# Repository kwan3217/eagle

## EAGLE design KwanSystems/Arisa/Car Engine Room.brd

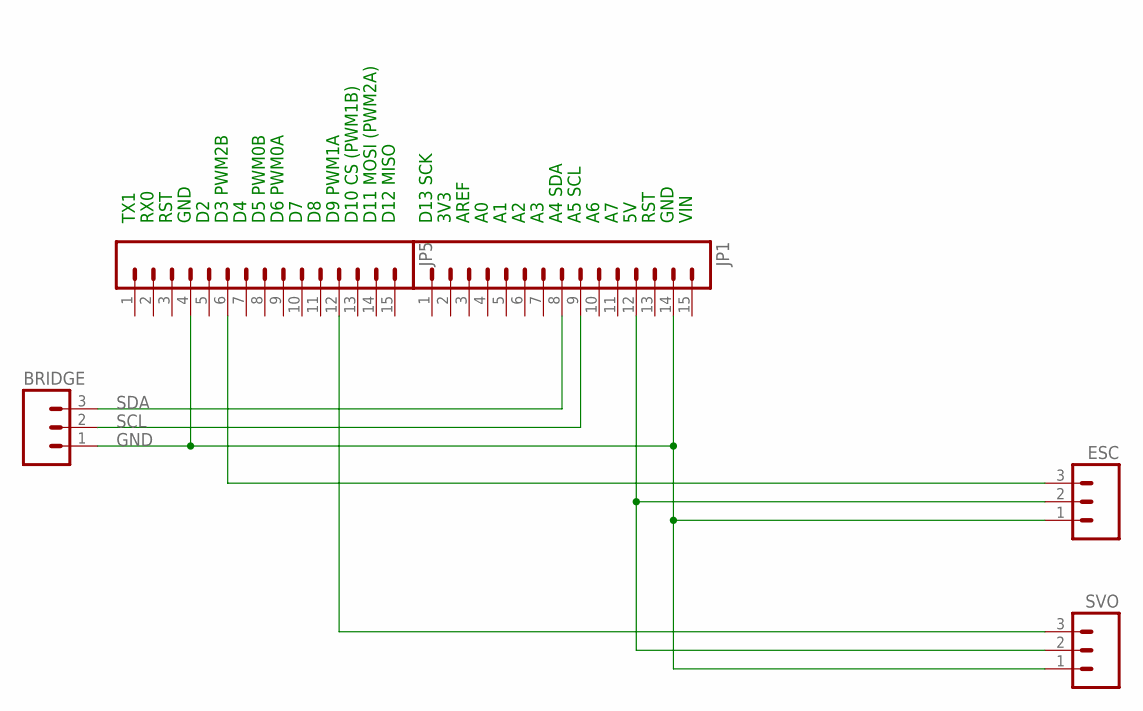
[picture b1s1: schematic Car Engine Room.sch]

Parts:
BRIDGE: M03PTH; 1X03
ESC: M03PTH; 1X03
JP1, JP5: M15; 1X15
SVO: M03PTH; 1X03

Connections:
GND: BRIDGE.1, ESC.1, JP1.14, JP5.4, SVO.1
IN1: ESC.3, JP5.6
IN2: JP5.12, SVO.3
SCL: BRIDGE.2, JP1.9
SDA: BRIDGE.3, JP1.8
VCC: ESC.2, JP1.12, SVO.2

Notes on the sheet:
VIN
GND
RST
A5 SCL
A4 SDA
AREF
3V3
D13 SCK
D12 MISO
D11 MOSI (PWM2A)
D10 CS (PWM1B)
D9 PWM1A
D6 PWM0A
D5 PWM0B
D3 PWM2B
RX0
TX1

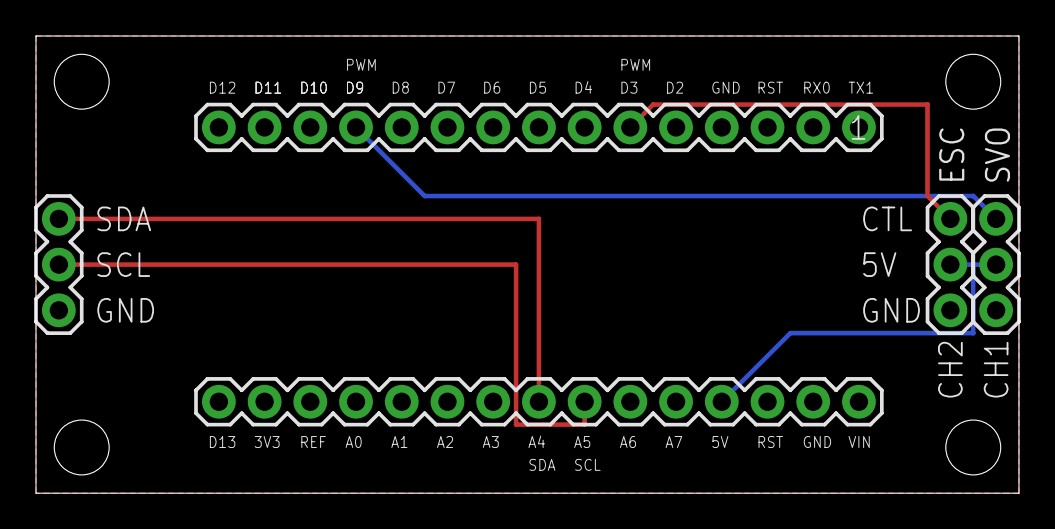
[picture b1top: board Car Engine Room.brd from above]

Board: 2 copper layers, 54.6 x 25.4 mm, 10 parts (1 on the bottom side), 6 nets.

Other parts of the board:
U$1, U$2, U$4, U$5: STAND-OFF-TIGHT
U$3: KWAN_CIRCLE

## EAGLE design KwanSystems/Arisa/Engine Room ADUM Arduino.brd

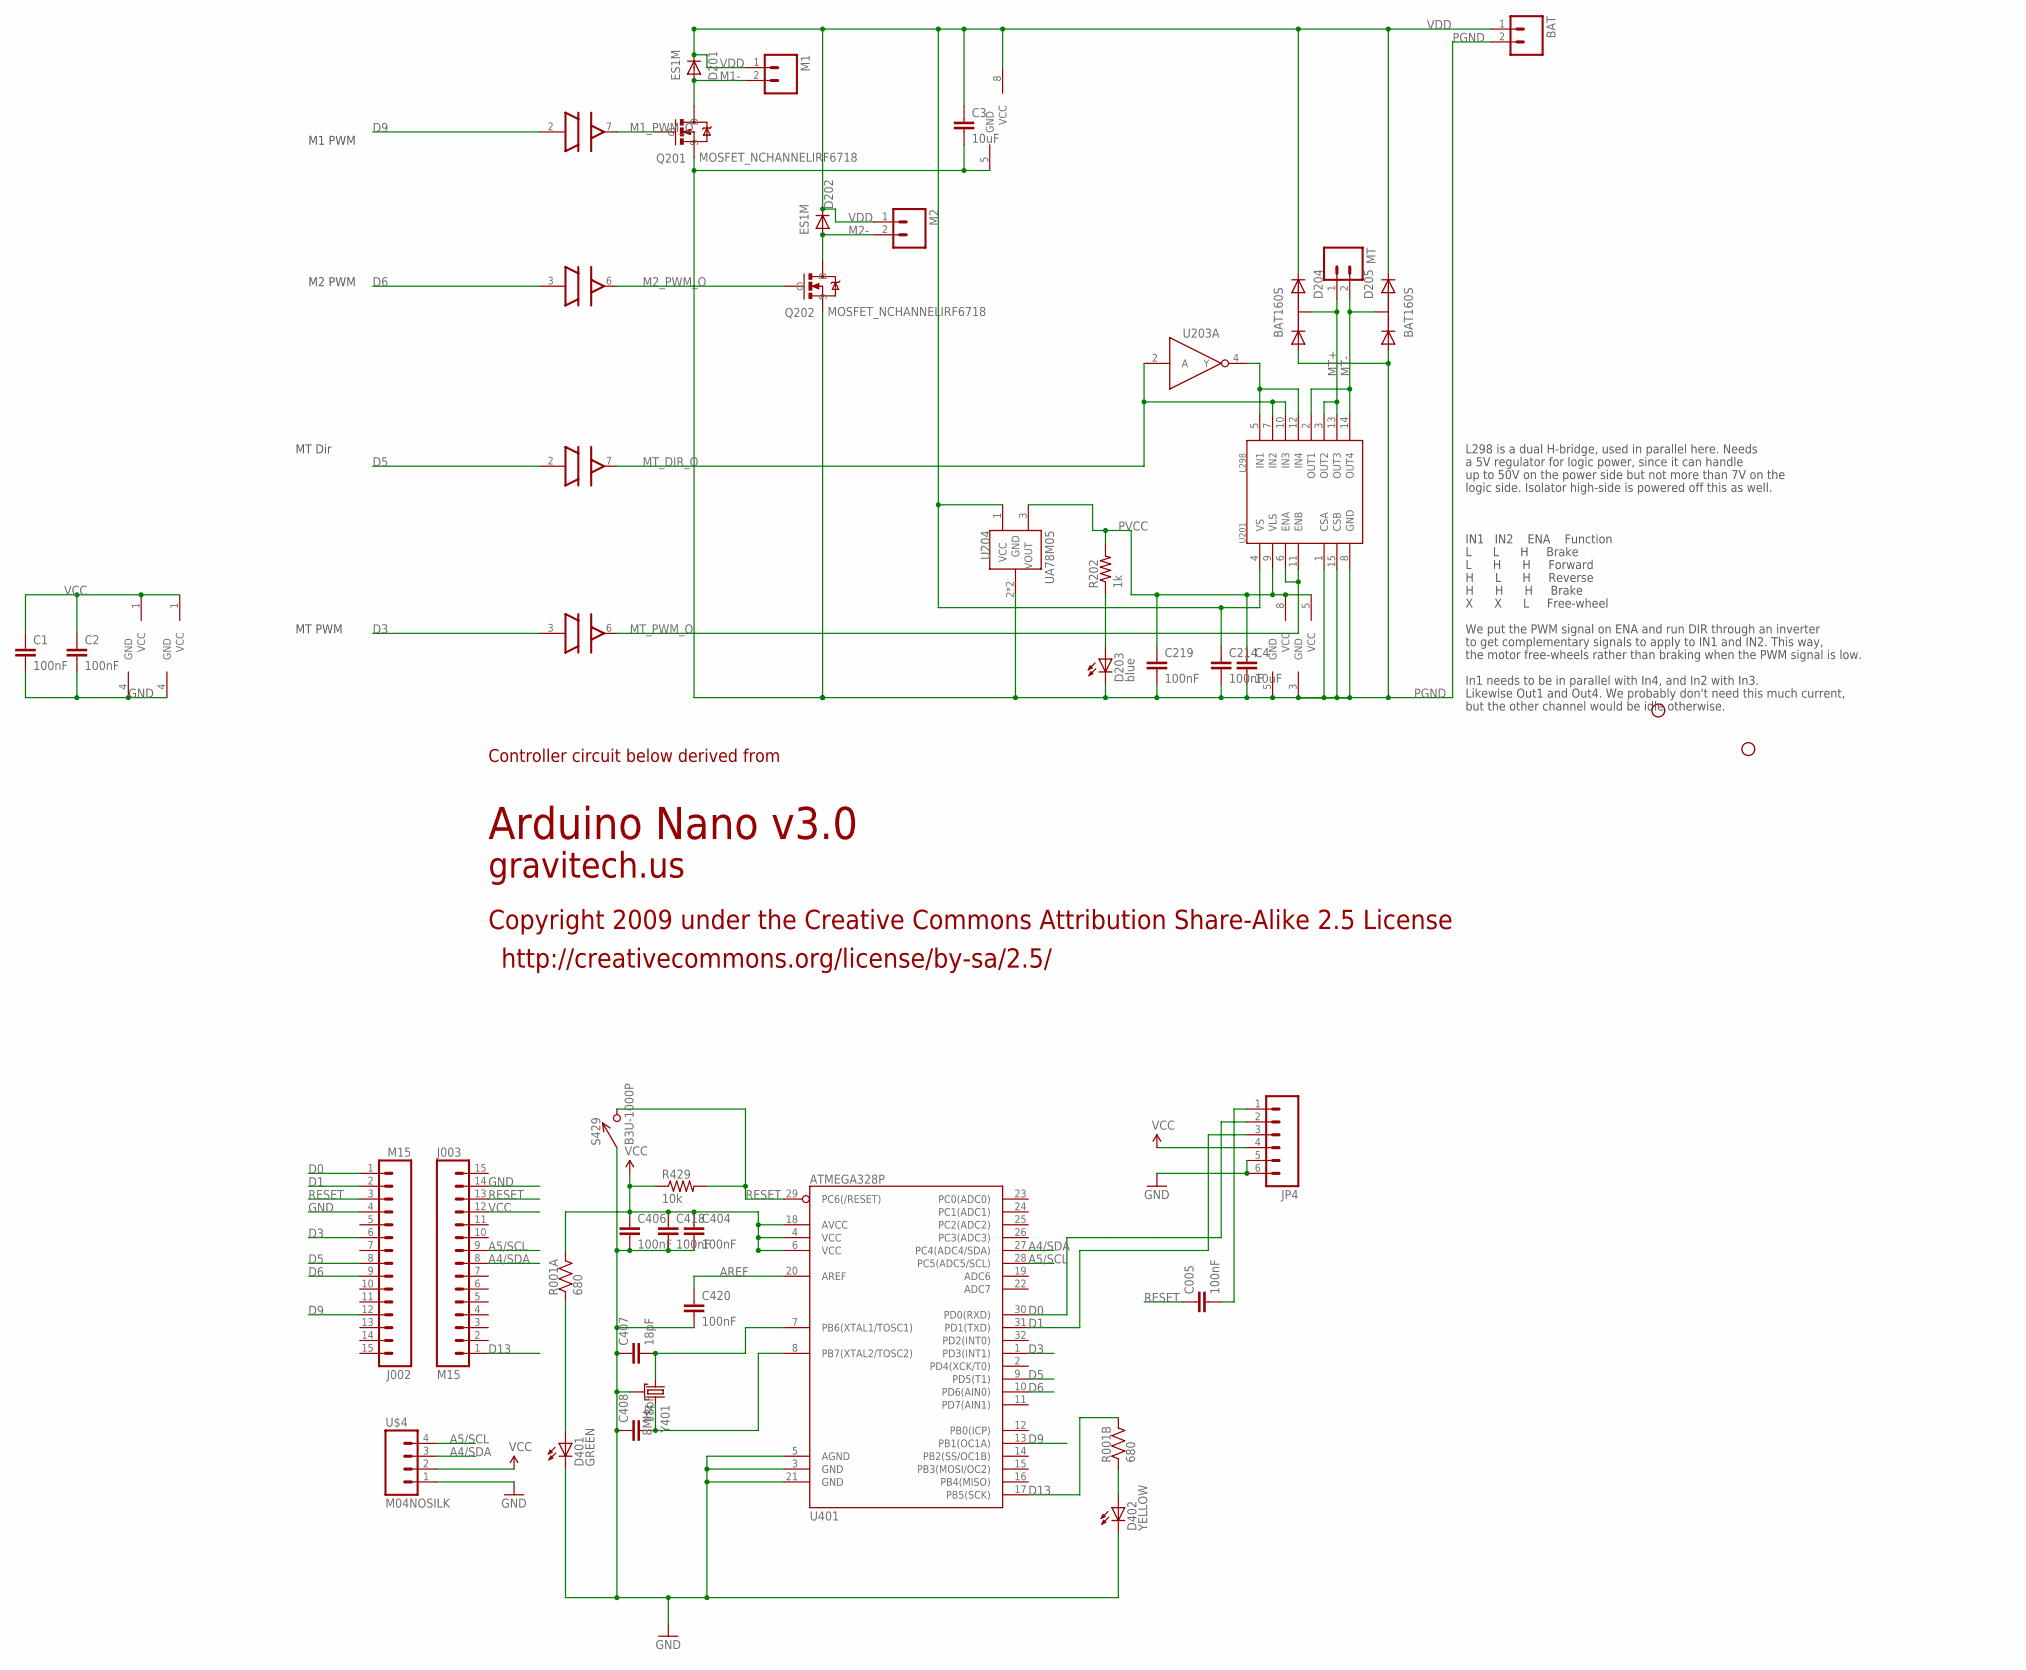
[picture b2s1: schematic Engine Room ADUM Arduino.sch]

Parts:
BAT: M02PTH4; 1X02_XTRA_BIG
C1, C2, C219: 100nF; 0402-CAP
C3, C4: 10uF; 1206
C005, C404, C406, C418, C420: 100nF; 0402-CAP; DIGIKEY 445-1268-1-ND
C214: 100nF; 1206
C407, C408: 18pF; 0402-CAP; DIGIKEY 445-1238-1-ND
D201, D202: ES1M; DO-214AC
D203: blue; LED-0603
D204, D205: BAT160S; SOT-223
D401: GREEN; LED-0603; DIGIKEY 350-2036-1-ND
D402: YELLOW; LED-0603; DIGIKEY 754-1124-1-ND
J002, J003: M15; 1X15; DIGIKEY $NOPART
JP1, JP2: STAND-OFF
JP4: M06SIP; 1X06
M1, M2: M02PTH4; 1X02_XTRA_BIG
MT: M02PTH; 1X02
Q201, Q202: MOSFET_NCHANNELIRF6718; DIRECTFET_L6
R001: 680; CRA02; DIGIKEY CRA4S8680CT-ND
R202: 1k; 0402-RES
R429: 10k; 0402-RES; DIGIKEY P10.0KLCT-ND
S429: B3U-1000P
U201: L298; MULTIWATT15
U203: MC74VHC1G04; SOT-23-5
U204: UA78M05; SOT-223
U401: ATMEGA328P; TQFP32-08; DIGIKEY ATMEGA328P-15AZCT-ND
U$3, U$5: ADUM3221; SO8N
U$4: M04NOSILK; M04SIP
Y401: 8MHz; CRYSTAL_SMD_2MM_2_5MM

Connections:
A4/SDA: J003.8, U401.27 (PC4(ADC4/SDA)), U$4.3
A5/SCL: J003.9, U401.28 (PC5(ADC5/SCL)), U$4.4
AREF: C420.1, U401.20 (AREF)
D0: J002.1, JP4.2, U401.30 (PD0(RXD))
D1: J002.2, JP4.3, U401.31 (PD1(TXD))
D3: J002.6, U401.1 (PD3(INT1)), U$5.3 (IN)
D5: J002.8, U401.9 (PD5(T1)), U$5.2 (IN)
D6: J002.9, U401.10 (PD6(AIN0)), U$3.3 (IN)
D9: J002.12, U401.13 (PB1(OC1A)), U$3.2 (IN)
D13: J003.1, R001.3 (2), U401.17 (PB5(SCK))
DTR#: C005.2, JP4.1
GND: C1.2, C2.2, C404.2, C406.2, C407.1, C408.1, C418.2, C420.2, D401.C, D402.C, J002.4, J003.14, JP4.5, JP4.6, S429.P$1 (1), U401.3 (GND), U401.5 (AGND), U401.21 (GND), U$3.4 (GND), U$4.1, U$5.4 (GND), Y401.2 (GND), Y401.4 (GND)
M1-: D201.A, M1.2, Q201.D1 (D), Q201.D2 (D)
M1_PWM_O: Q201.G, U$3.7 (OUT)
M2-: D202.A, M2.2, Q202.D1 (D), Q202.D2 (D)
M2_PWM_O: Q202.G, U$3.6 (OUT)
MT+: D204.4 (K1A2), MT.1, U201.3 (OUT2), U201.13 (OUT3)
MT-: D205.4 (K1A2), MT.2, U201.2 (OUT1), U201.14 (OUT4)
MT_DIR_O: U201.7 (IN2), U201.10 (IN3), U203.2 (A), U$5.7 (OUT)
MT_PWM_O: U201.6 (ENA), U201.11 (ENB), U$5.6 (OUT)
unnamed: D203.A, R202.1
unnamed: U201.5 (IN1), U201.12 (IN4), U203.4 (Y)
unnamed: C407.2, U401.7 (PB6(XTAL1/TOSC1)), Y401.1
unnamed: C408.2, U401.8 (PB7(XTAL2/TOSC2)), Y401.3 (2)
unnamed: D401.A, R001.1
unnamed: D402.A, R001.2 (1)
PGND: BAT.2, C3.2, C4.2, C214.2, C219.2, D203.C, D204.1 (A1), D205.1 (A1), Q201.S, Q202.S, U201.1 (CSA), U201.8 (GND), U201.15 (CSB), U203.3 (GND), U204.2 (GND), U204.4 (GND), U$3.5 (GND), U$5.5 (GND)
PVCC: C4.1, C219.1, R202.2, U201.9 (VLS), U203.5 (VCC), U204.3 (VOUT), U$5.8 (VCC)
RESET: C005.1, J002.3, J003.13, R429.2, S429.P$2 (2), U401.29 (PC6(/RESET))
VCC: C1.1, C2.1, C404.1, C406.1, C418.1, J003.12, JP4.4, R001.4 (2), R429.1, U401.4 (VCC), U401.6 (VCC), U401.18 (AVCC), U$3.1 (VCC), U$4.2, U$5.1 (VCC)
VDD: BAT.1, C3.1, C214.1, D201.C, D202.C, D204.3 (K2), D205.3 (K2), M1.1, M2.1, U201.4 (VS), U204.1 (VCC), U$3.8 (VCC)

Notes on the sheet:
M1 PWM
M2 PWM
MT Dir
MT PWM
L298 is a dual H-bridge, used in parallel here. Needs
a 5V regulator for logic power, since it can handle
up to 50V on the power side but not more than 7V on the
logic side. Isolator high-side is powered off this as well.
IN1 IN2 ENA Function
L L H Brake
L H H Forward
H L H Reverse
H H H Brake
X X L Free-wheel
We put the PWM signal on ENA and run DIR through an inverter
to get complementary signals to apply to IN1 and IN2. This way,
the motor free-wheels rather than braking when the PWM signal is low.
In1 needs to be in parallel with In4, and In2 with In3.
Likewise Out1 and Out4. We probably don't need this much current,
but the other channel would be idle otherwise.
Arduino Nano v3.0
Copyright 2009 under the Creative Commons Attribution Share-Alike 2.5 License
http://creativecommons.org/license/by-sa/2.5/
Controller circuit below derived from
gravitech.us

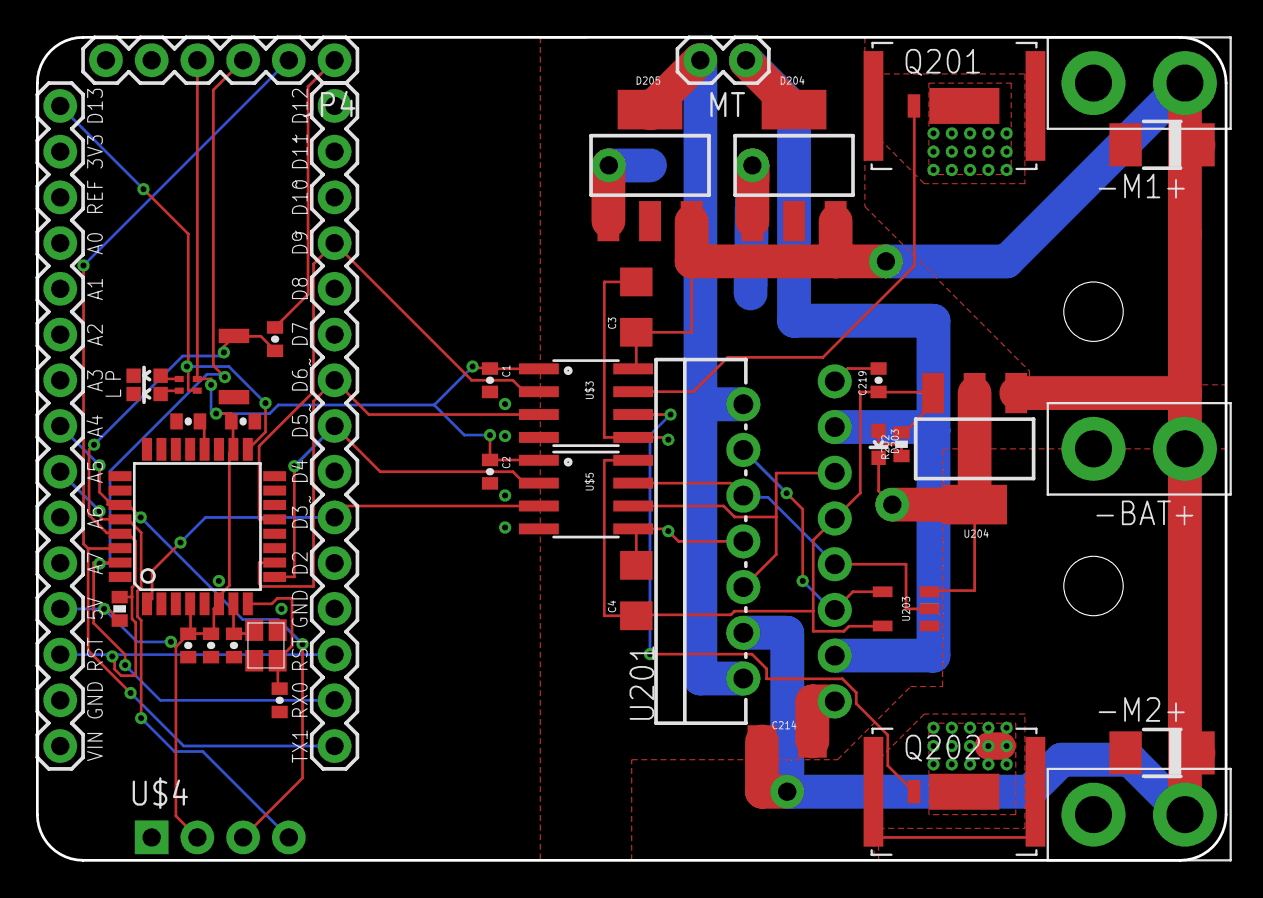
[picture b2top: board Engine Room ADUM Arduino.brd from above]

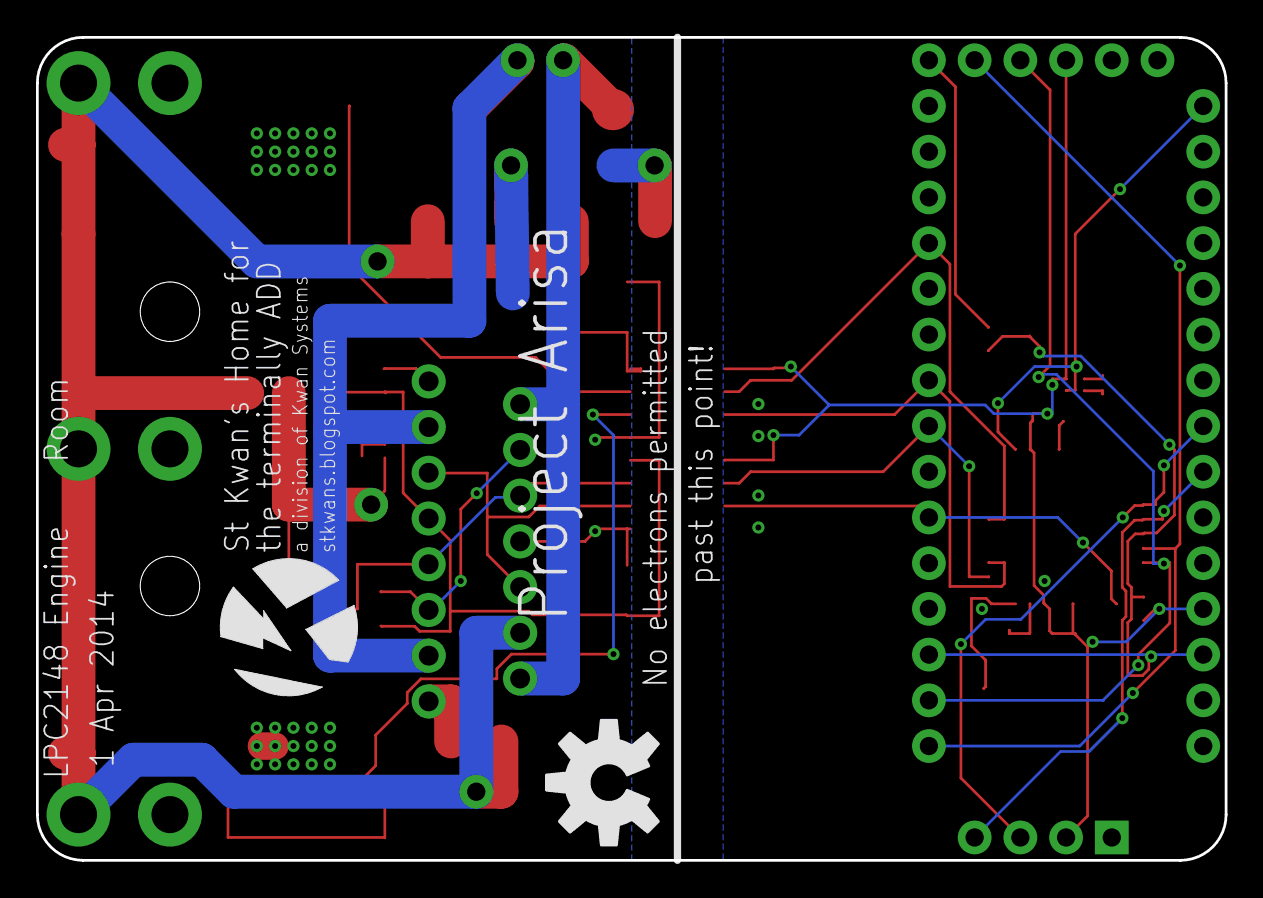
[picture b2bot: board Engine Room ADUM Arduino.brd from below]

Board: 2 copper layers, 66.0 x 45.7 mm, 45 parts (2 on the bottom side), 31 nets.

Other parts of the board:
U$1: KWAN_CIRCLE
U$2: OSHW-LOGO-L

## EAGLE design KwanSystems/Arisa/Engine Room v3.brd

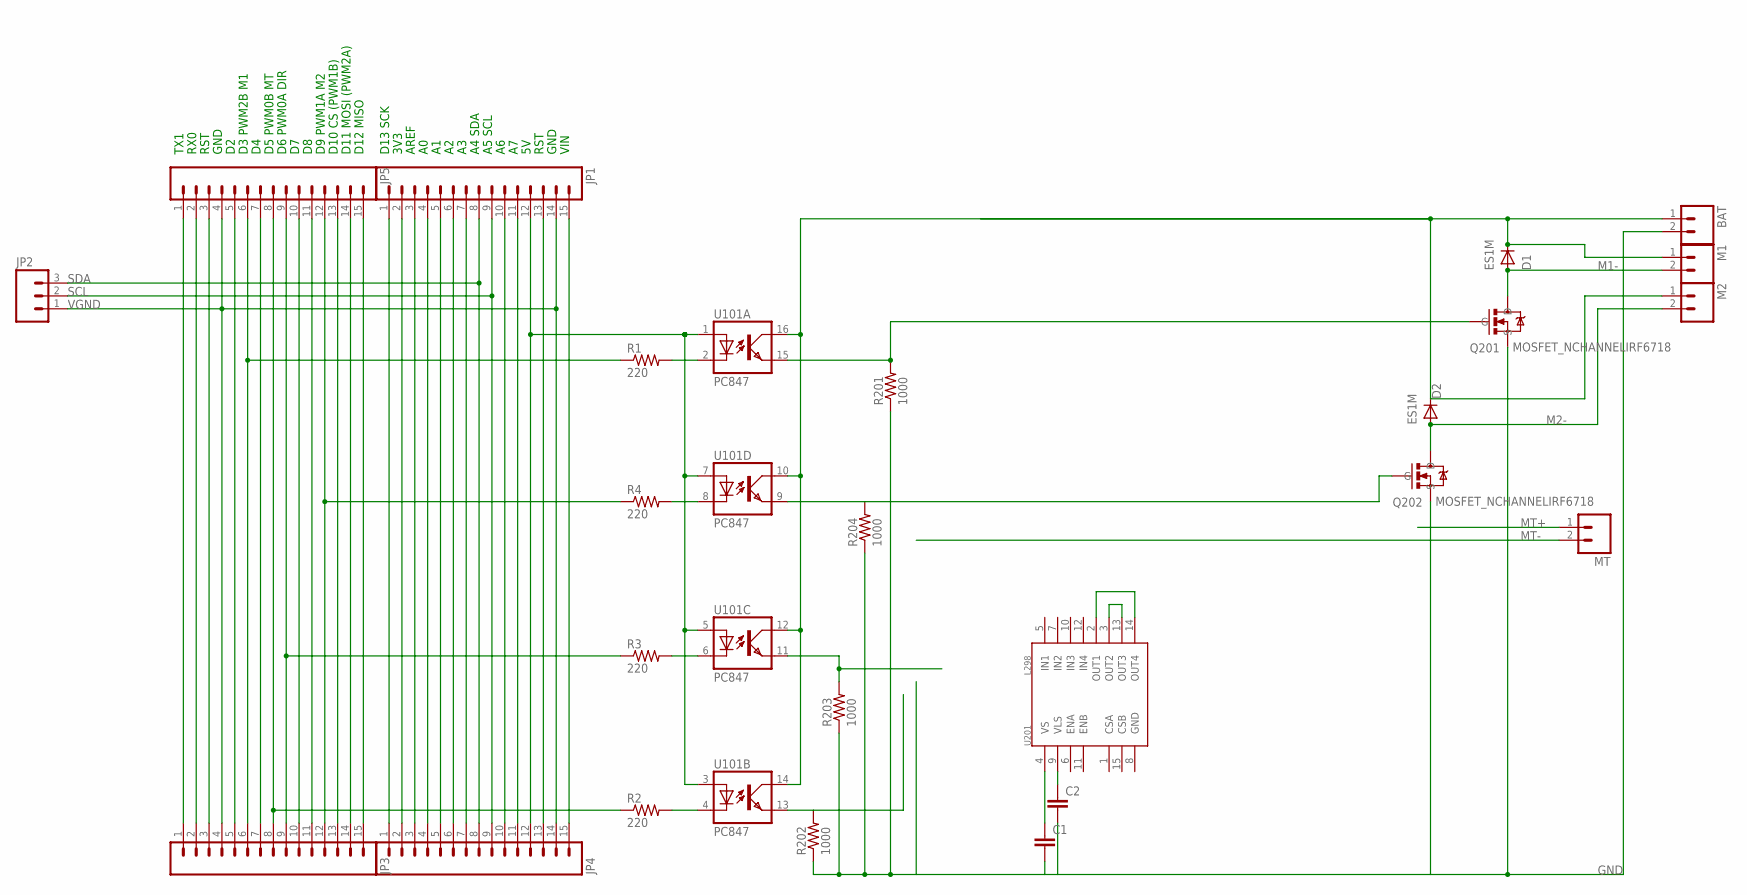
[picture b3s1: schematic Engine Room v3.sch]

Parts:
BAT: M02PTH4; 1X02_XTRA_BIG
C1, C2: CAP0402-CAP; 0402-CAP
D1, D2: ES1M; DO-214AC
JP1, JP5: M15LOCK; 1X15_LOCK
JP2: M03LOCK; 1X03_LOCK
JP3, JP4: M15; 1X15
M1, M2: M02PTH4; 1X02_XTRA_BIG
MT: M02PTH; 1X02
Q201, Q202: MOSFET_NCHANNELIRF6718; DIRECTFET_L6
R1, R2, R3, R4: 220; 0402-RES
R201, R202, R203, R204: 1000; 0402-RES
U101: PC847; DIL16
U201: L298; MULTIWATT15

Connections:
GND: BAT.2, C1.2, C2.2, Q201.S, Q202.S, R201.1, R202.1, R203.1, R204.1
IN1: JP3.6, JP5.6, R1.1
IN2: JP3.12, JP5.12, R4.1
IN3: JP3.8, JP5.8, R2.1
M1-: D1.A, M1.2, Q201.D1 (D), Q201.D2 (D)
M2-: D2.A, M2.2, Q202.D1 (D), Q202.D2 (D)
MT+: MT.1
MT-: MT.2
unnamed: R4.2, U101.8 (C)
unnamed: R3.2, U101.6 (C)
unnamed: R1.2, U101.2 (C)
unnamed: R2.2, U101.4 (C)
unnamed: JP1.15, JP4.15
unnamed: Q201.G, R201.2, U101.15 (EMIT)
unnamed: U201.2 (OUT1), U201.14 (OUT4)
unnamed: Q202.G, R204.2, U101.9 (EMIT)
unnamed: U201.3 (OUT2), U201.13 (OUT3)
unnamed: R203.2, U101.11 (EMIT)
unnamed: JP3.9, JP5.9, R3.1
unnamed: JP3.1, JP5.1
unnamed: JP3.2, JP5.2
unnamed: JP3.3, JP5.3
unnamed: R202.2, U101.13 (EMIT)
unnamed: C2.1, U201.9 (VLS)
unnamed: C1.1, U201.4 (VS)
unnamed: JP3.5, JP5.5
unnamed: JP3.15, JP5.15
unnamed: JP3.14, JP5.14
unnamed: JP3.13, JP5.13
unnamed: JP3.7, JP5.7
unnamed: JP3.10, JP5.10
unnamed: JP3.11, JP5.11
unnamed: JP1.13, JP4.13
unnamed: JP1.11, JP4.11
unnamed: JP1.10, JP4.10
unnamed: JP1.7, JP4.7
unnamed: JP1.6, JP4.6
unnamed: JP1.5, JP4.5
unnamed: JP1.4, JP4.4
unnamed: JP1.3, JP4.3
unnamed: JP1.2, JP4.2
unnamed: JP1.1, JP4.1
SCL: JP1.9, JP2.2, JP4.9
SDA: JP1.8, JP2.3, JP4.8
VCC: JP1.12, JP4.12, U101.1 (A), U101.3 (A), U101.5 (A), U101.7 (A)
VDD: BAT.1, D1.C, D2.C, M1.1, M2.1, U101.10 (COL), U101.12 (COL), U101.14 (COL), U101.16 (COL)
VGND: JP1.14, JP2.1, JP3.4, JP4.14, JP5.4

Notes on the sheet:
VIN
GND
RST
A5 SCL
A4 SDA
AREF
3V3
D13 SCK
D12 MISO
D11 MOSI (PWM2A)
D10 CS (PWM1B)
D9 PWM1A M2
D6 PWM0A DIR
D5 PWM0B MT
D3 PWM2B M1
RX0
TX1

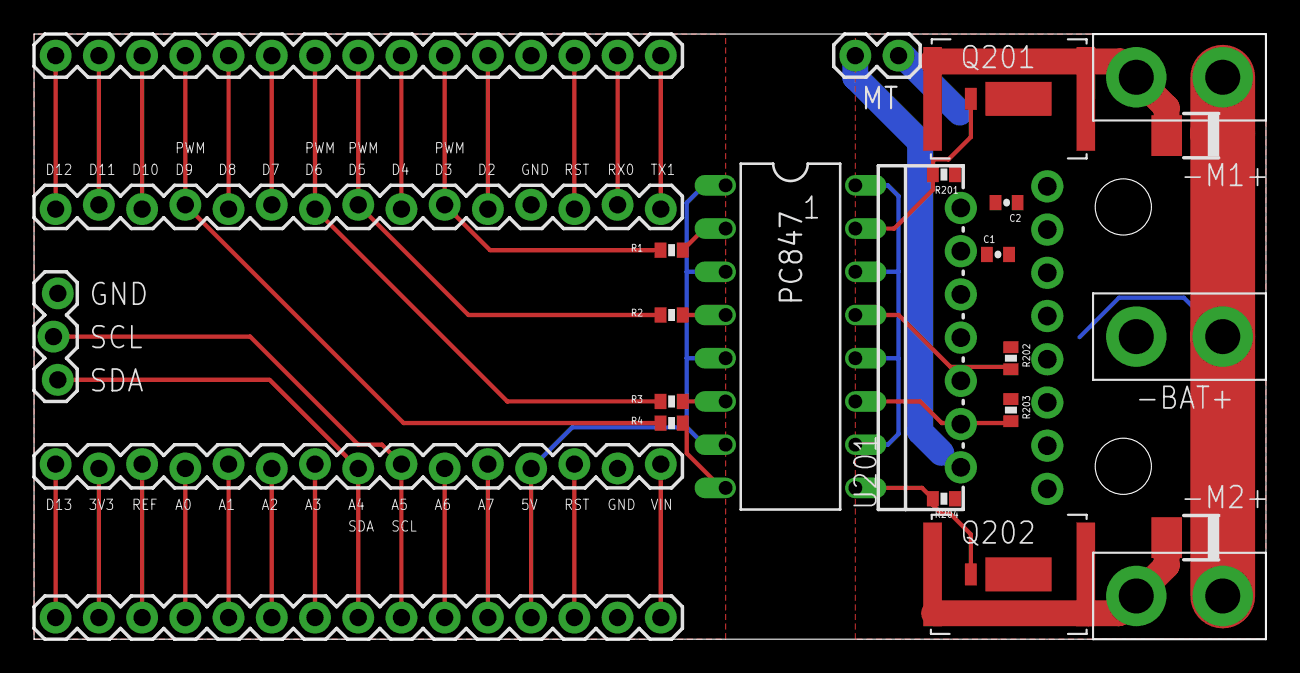
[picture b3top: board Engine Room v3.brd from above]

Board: 2 copper layers, 72.4 x 35.6 mm, 28 parts (1 on the bottom side), 45 nets.

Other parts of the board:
U$1, U$2: STAND-OFF
U$3: KWAN_CIRCLE

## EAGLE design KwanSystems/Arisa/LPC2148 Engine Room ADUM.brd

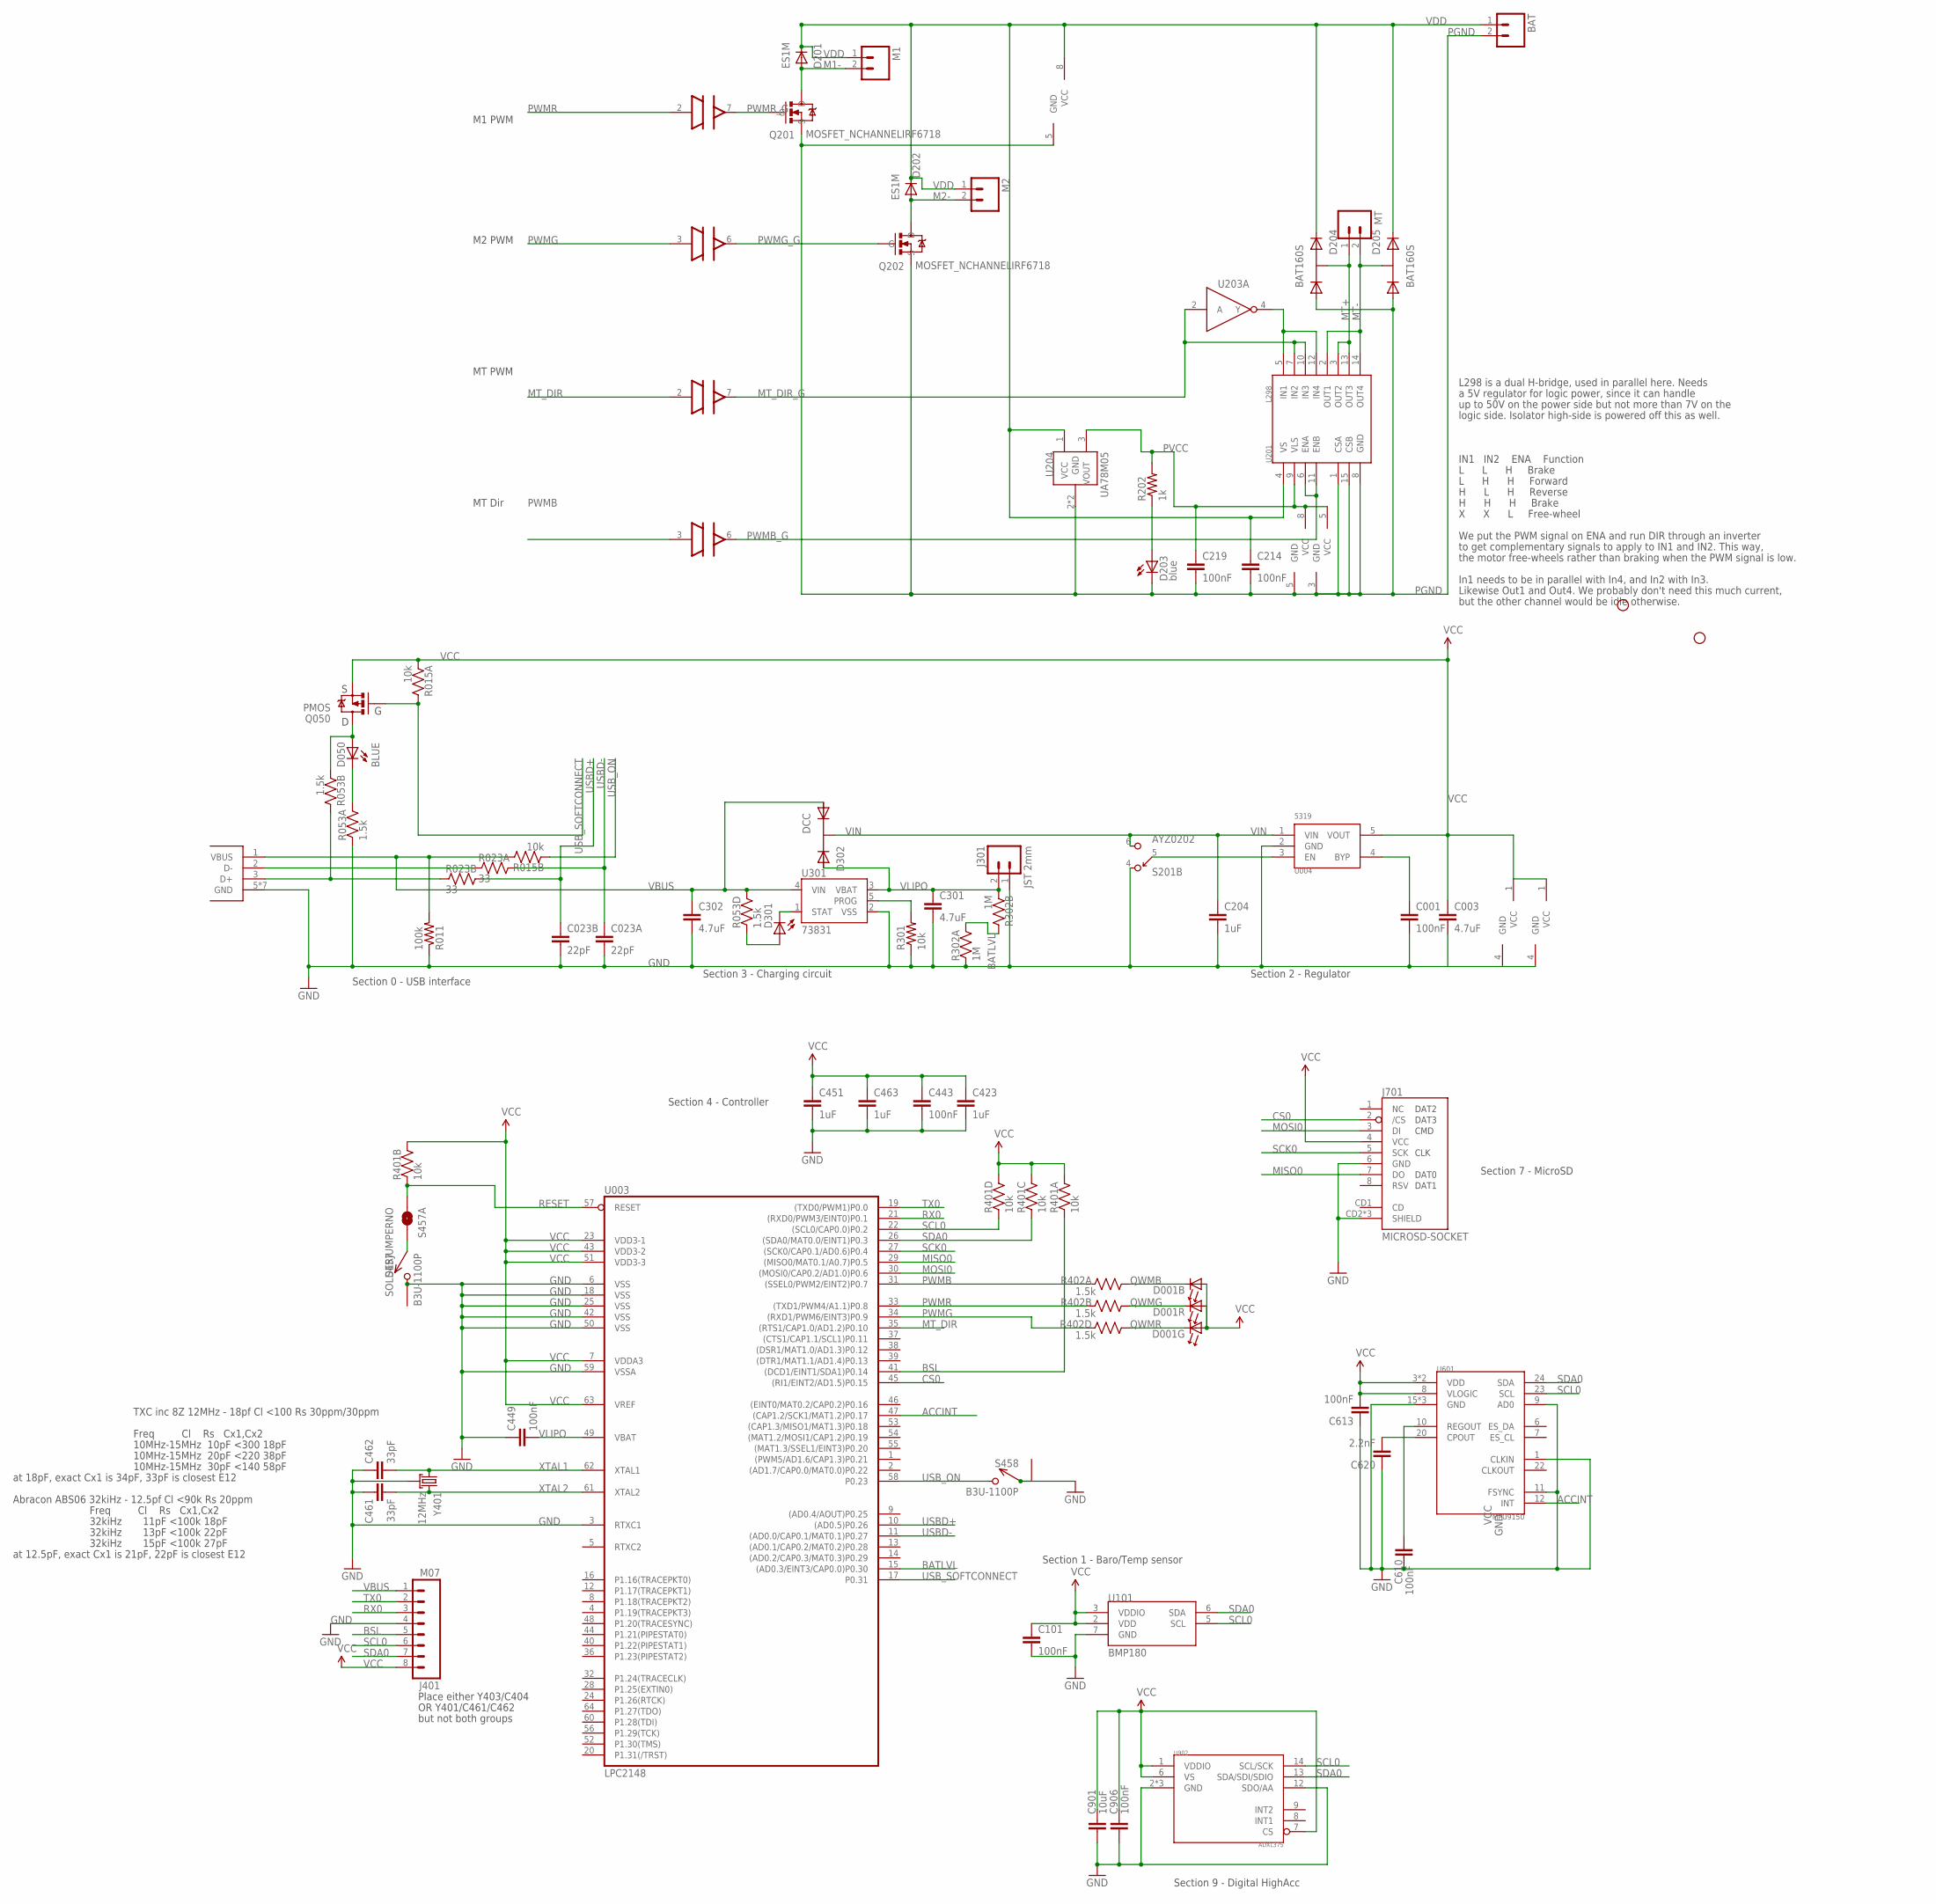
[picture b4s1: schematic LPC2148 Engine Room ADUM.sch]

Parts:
BAT: M02PTH4; 1X02_XTRA_BIG
C001, C101, C443, C449, C610, C613, C906: 100nF; 0402-CAP; DIGIKEY 445-1265-1-ND
C003, C301, C302: 4.7uF; 0402-CAP; DIGIKEY 445-7395-1-ND
C023: 22pF; CKCM25; DIGIKEY 445-1860-1-ND
C204, C423, C451, C463: 1uF; 0402-CAP; DIGIKEY 445-4114-1-ND
C214, C219: 100nF; 0402-CAP
C461, C462: 33pF; 0402-CAP; DIGIKEY 445-1241-1-ND
C620: 2.2nF; 0402-CAP; DIGIKEY 445-1257-1-ND
C901: 10uF; 0603-CAP; DIGIKEY 445-7486-1-ND
D001: SMLP36RGB2W(R); SMLP36; DIGIKEY 846-1097-1-ND
D050: BLUE; LED-0603; DIGIKEY 350-2037-1-ND
D201, D202: ES1M; DO-214AC
D203: blue; LED-0603
D204, D205: BAT160S; SOT-223
D301: YELLOW; LED-0603; DIGIKEY 350-2032-1-ND
D302: DCC; SOT-23-3; DIGIKEY 568-6500-1-ND
J004: USB_MICROB_JSTGCT; USB_MICROB_3075; DIGIKEY 609-4616-2-ND
J301: JST 2mm; JST-2-SMD; DIGIKEY 455-1749-1-ND
J401: M07; 1X08; DIGIKEY $NOPART
J701: MICROSD-SOCKET; MICROSD-SOCKET-PP; DIGIKEY 101-00581-59-1-ND
JP1, JP2: STAND-OFF
M1, M2: M02PTH4; 1X02_XTRA_BIG
MT: M02PTH; 1X02
Q050: PMOS; SOT23-3; DIGIKEY NTR1P02T1GOSCT-ND
Q201, Q202: MOSFET_NCHANNELIRF6718; DIRECTFET_L6
R011: 100k; 0402-RES; DIGIKEY P100KLCT-ND
R015: 10k; CRA02; DIGIKEY Y5103CT-ND
R023: 33; CRA02
R053, R402: 1.5k; CRA04; DIGIKEY CRA4S81.5KCT-ND
R202: 1k; 0402-RES
R301: 10k; 0402-RES; DIGIKEY P10.0KLCT-ND
R302: 1M; CRA02
R401: 10k; CRA04; DIGIKEY CRA4S810KCT-ND
S201: AYZ0202; DIGIKEY 401-2013-1-ND
S457, S458: B3U-1100P; DIGIKEY SW1021CT-ND
S457A: SOLDERJUMPERNO; SJ_2S-NO; DIGIKEY $NOPART
U003: LPC2148; SQFP-S-10X10-64; DIGIKEY 568-1765-ND
U004: 5319; SOT-23-5; DIGIKEY 576-1910-1-ND
U101: BMP180; DIGIKEY 828-1027-1-ND
U201: L298; MULTIWATT15
U203: MC74VHC1G04; SOT-23-5
U204: UA78M05; SOT-223
U301: 73831; SOT23-5; DIGIKEY MCP73831T-2ACI/OTCT-ND
U601: MPU9150; LLGA24; DIGIKEY $NOPART
U902: ADXL375; DIGIKEY ADXL375BCCZ-ND
U$3, U$5: ADUM3221; SO8N
Y401: 12MHz; CRYSTAL_SMD_2MM_2_5MM; DIGIKEY 887-1487-1-ND

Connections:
ACCINT: U003.47 ((CAP1.2/SCK1/MAT1.2)P0.17), U601.12 (INT)
BATLVL: R302.3 (2), R302.4 (2), U003.15 ((AD0.3/EINT3/CAP0.0)P0.30)
BSL: J401.5, R401.1, U003.41 ((DCD1/EINT1/SDA1)P0.14)
CONN_D+: J004.3 (D+), R023.2 (1), R053.7 (2)
CONN_D-: J004.2 (D-), R023.1
CS0: J701.2 (/CS), U003.45 ((RI1/EINT2/AD1.5)P0.15)
EN: S201.5, U004.3 (EN)
GND: C001.2, C003.2, C023.3 (2), C023.4 (2), C101.2, C204.2, C301.2, C302.2, C423.2, C443.2, C449.1, C451.2, C461.1, C462.1, C463.2, C610.2, C613.1, C620.1, C901.2, C906.2, J004.5 (GND), J004.P$1 (GND), J004.P$2 (GND), J004.P$3 (GND), J004.P$4 (GND), J004.P$8 (GND), J004.P$10 (GND), J301.1, J401.4, J701.6 (GND), J701.CD2 (SHIELD), J701.GND1 (SHIELD), J701.GND3 (SHIELD), R011.1, R053.1, R301.1, R302.1, S201.4, S457.P$2 (2), S457.P$3 (1), S458.P$1 (1), S458.P$3 (1), U003.3 (RTXC1), U003.6 (VSS), U003.18 (VSS), U003.25 (VSS), U003.42 (VSS), U003.50 (VSS), U003.59 (VSSA), U004.2 (GND), U101.7 (GND), U301.2 (VSS), U601.1 (CLKIN), U601.9 (AD0), U601.11 (FSYNC), U601.15 (GND), U601.17 (GND), U601.18 (GND), U902.2 (GND), U902.4 (GND), U902.5 (GND), U902.12 (SDO/AA), U$3.4 (GND), U$5.4 (GND), Y401.2 (GND), Y401.4 (GND)
M1-: D201.A, M1.2, Q201.D1 (D), Q201.D2 (D)
M2-: D202.A, M2.2, Q202.D1 (D), Q202.D2 (D)
MISO0: J701.7 (DO), U003.29 ((MISO0/MAT0.1/A0.7)P0.5)
MOSI0: J701.3 (DI), U003.30 ((MOSI0/CAP0.2/AD1.0)P0.6)
MT+: D204.4 (K1A2), MT.1, U201.3 (OUT2), U201.13 (OUT3)
MT-: D205.4 (K1A2), MT.2, U201.2 (OUT1), U201.14 (OUT4)
MT_DIR: U003.35 ((RTS1/CAP1.0/AD1.2)P0.10), U$5.2 (IN)
MT_DIR_G: U201.7 (IN2), U201.10 (IN3), U203.2 (A), U$5.7 (OUT)
unnamed: D203.A, R202.1
unnamed: U201.5 (IN1), U201.12 (IN4), U203.4 (Y)
unnamed: C620.2, U601.20 (CPOUT)
unnamed: C610.1, U601.10 (REGOUT)
unnamed: S457.P$1 (1), S457A.2
unnamed: R301.2, U301.5 (PROG)
unnamed: D050.C, R053.8 (2)
unnamed: C001.1, U004.4 (BYP)
unnamed: D301.A, R053.4 (1)
unnamed: D301.C, U301.1 (STAT)
unnamed: D050.A, Q050.3 (D), R053.2 (1)
PGND: BAT.2, C214.2, C219.2, D203.C, D204.1 (A1), D205.1 (A1), Q201.S, Q202.S, U201.1 (CSA), U201.8 (GND), U201.15 (CSB), U203.3 (GND), U204.2 (GND), U204.4 (GND), U$3.5 (GND), U$5.5 (GND)
PVCC: C219.1, R202.2, U201.9 (VLS), U203.5 (VCC), U204.3 (VOUT), U$5.8 (VCC)
PWMB: R402.8 (2), U003.31 ((SSEL0/PWM2/EINT2)P0.7), U$5.3 (IN)
PWMB_G: U201.6 (ENA), U201.11 (ENB), U$5.6 (OUT)
PWMG: R402.5 (2), U003.34 ((RXD1/PWM6/EINT3)P0.9), U$3.3 (IN)
PWMG_G: Q202.G, U$3.6 (OUT)
PWMR: R402.7 (2), U003.33 ((TXD1/PWM4/A1.1)P0.8), U$3.2 (IN)
PWMR_G: Q201.G, U$3.7 (OUT)
QWMB: D001.1 (C), R402.1
QWMG: D001.5 (C), R402.4 (1)
QWMR: D001.3 (C), R402.2 (1)
RESET: R401.2 (1), S457A.1, U003.57 (RESET)
RX0: J401.3, U003.21 ((RXD0/PWM3/EINT0)P0.1)
SCK0: J701.5 (SCK), U003.27 ((SCK0/CAP0.1/AD0.6)P0.4)
SCL0: J401.6, R401.4 (1), U003.22 ((SCL0/CAP0.0)P0.2), U101.5 (SCL), U601.23 (SCL), U902.14 (SCL/SCK)
SDA0: J401.7, R401.3 (1), U003.26 ((SDA0/MAT0.0/EINT1)P0.3), U101.6 (SDA), U601.24 (SDA), U902.13 (SDA/SDI/SDIO)
TX0: J401.2, U003.19 ((TXD0/PWM1)P0.0)
USBD+: C023.2 (1), R023.3 (2), U003.10 ((AD0.5)P0.26)
USBD-: C023.1, R023.4 (2), U003.11 ((AD0.0/CAP0.1/MAT0.1)P0.27)
USB_ON: R015.2 (1), S458.P$2 (2), U003.58 (P0.23)
USB_SOFTCONNECT: Q050.1 (G), R015.4 (2), U003.17 (P0.31)
VBUS: C302.1, D302.1 (A1), J004.1 (VBUS), J401.1, R011.2, R015.3 (2), R053.5 (2), U301.4 (VIN)
VCC: C003.1, C101.1, C423.1, C443.1, C451.1, C463.1, C613.2, C901.1, C906.1, D001.2 (A), D001.4 (A), D001.6 (A), J401.8, J701.4 (VCC), Q050.2 (S), R015.1, R401.5 (2), R401.6 (2), R401.7 (2), R401.8 (2), U003.7 (VDDA3), U003.23 (VDD3-1), U003.43 (VDD3-2), U003.51 (VDD3-3), U003.63 (VREF), U004.5 (VOUT), U101.2 (VDD), U101.3 (VDDIO), U601.3 (VDD), U601.8 (VLOGIC), U601.13 (VDD), U902.1 (VDDIO), U902.6 (VS), U902.7 (CS), U$3.1 (VCC), U$5.1 (VCC)
VDD: BAT.1, C214.1, D201.C, D202.C, D204.3 (K2), D205.3 (K2), M1.1, M2.1, U201.4 (VS), U204.1 (VCC), U$3.8 (VCC)
VIN: C204.1, D302.3 (K), S201.6, U004.1 (VIN)
VLIPO: C301.1, C449.2, D302.2 (A2), J301.2, R302.2 (1), U003.49 (VBAT), U301.3 (VBAT)
XTAL1: C462.2, U003.62 (XTAL1), Y401.1
XTAL2: C461.2, U003.61 (XTAL2), Y401.3 (2)

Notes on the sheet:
M1 PWM
M2 PWM
MT Dir
MT PWM
Section 4 - Controller
Section 7 - MicroSD
Section 1 - Baro/Temp sensor
Freq Cl Rs Cx1,Cx2
10MHz-15MHz 10pF <300 18pF
10MHz-15MHz 20pF <220 38pF
10MHz-15MHz 30pF <140 58pF
TXC inc 8Z 12MHz - 18pf Cl <100 Rs 30ppm/30ppm
at 18pF, exact Cx1 is 34pF, 33pF is closest E12
32kiHz 11pF <100k 18pF
32kiHz 13pF <100k 22pF
32kiHz 15pF <100k 27pF
Abracon ABS06 32kiHz - 12.5pf Cl <90k Rs 20ppm
at 12.5pF, exact Cx1 is 21pF, 22pF is closest E12
Section 2 - Regulator
Section 3 - Charging circuit
Section 0 - USB interface
Place either Y403/C404
OR Y401/C461/C462
but not both groups
Section 9 - Digital HighAcc
L298 is a dual H-bridge, used in parallel here. Needs
a 5V regulator for logic power, since it can handle
up to 50V on the power side but not more than 7V on the
logic side. Isolator high-side is powered off this as well.
IN1 IN2 ENA Function
L L H Brake
L H H Forward
H L H Reverse
H H H Brake
X X L Free-wheel
We put the PWM signal on ENA and run DIR through an inverter
to get complementary signals to apply to IN1 and IN2. This way,
the motor free-wheels rather than braking when the PWM signal is low.
In1 needs to be in parallel with In4, and In2 with In3.
Likewise Out1 and Out4. We probably don't need this much current,

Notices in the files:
parts and their libraries:
SparkFun-Passives: Licensing: CC v3.0 Share-Alike You are welcome to use this library for commercial purposes.
